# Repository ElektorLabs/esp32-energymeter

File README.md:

# ESP32 Energy Meter

Welcome to the official repository for the ESP32 Energy Meter, an energy monitoring project developed by Elektor Labs. This repository hosts all the necessary design files, code, and documentation to build and deploy a safe energy meter using the ESP32-S3 microcontroller.

## Project Overview

The ESP32 Energy Meter utilizes the Espressif ESP32-S3 microcontroller and the ATM90E32AS IC from Microchip for precise energy measurement across single and three-phase systems. This version includes significant safety and functionality enhancements, including a transformer-based power supply and modularity for diverse applications.

## Features

- **High Precision:** Uses ATM90E32AS IC for accurate energy data.
- **Enhanced Safety:** Transformer-based power reduces direct exposure to high voltages.
- **Flexible Configuration:** Supports both single-phase and three-phase installations.
- **Smart Home Integration:** Easily integrates with Home Assistant for advanced energy management.
- **Customizable Firmware:** Includes ESPHome YAML configurations for easy adaptation and updates.

## Repository Contents

- `/hardware` - Electronic schematic files.
- `/hardware` - PCB design files suitable for manufacturing.
- `/src/ESPHome` - ESPHome YAML configuration files.

## Getting Started

### Prerequisites

Components used in this project are mention in the BOM list `/hardware/production/BOM-esp32-energymeter-V2.xlsx`, overview of the components and required tools are as follows:
- ESP32-S3 module
- ATM90E32AS IC
- Step-down transformer (220V AC to 12V AC) - Preferably a bell transformer
- Current Transfomers - YDHC SCT 013 100A 50mA
- Passive components (resistors, capacitors)
- Tools for PCB assembly and soldering

### Setup Instructions

1. **Clone the repository:**
   ```bash
   git clone https://github.com/ElektorLabs/esp32-energymeter.git
   ```
2. **PCB Assembly:**
   - Refer to the `/hardware` directory and manufacture the PCB using the provided design files.
   - Solder the components onto the PCB as per the layout and schematic details in the `/Schematics` folder.

3. **Firmware Installation:**
   - Navigate to the `/src/ESPHome` directory.
   - Update the YAML file with your specific network details and preferences.
   - Flash the firmware to the ESP32-S3 using ESPHome through the command line or ESPHome Dashboard.

4. **Integrate with Home Assistant:**
   - Follow the integration guide in the article to connect the energy meter to Home Assistant.
   - Monitor and manage your energy consumption directly through the Home Assistant interface.

## Calibration and Testing

- After assembly, perform a calibration check as described in the article to ensure accuracy.
- Test the device under different load conditions to verify the setup and adjust the calibration if necessary.

## Contributing

Your contributions are welcome! If you have enhancements, fixes, or improvements, please fork this repository and submit a pull request with your changes. For substantial modifications or new features, please open an issue to discuss them first.

## License

This project is distributed under the MIT License - see the LICENSE file for details.

## Acknowledgments

- Thanks to Espressif Systems for the ESP32 technology.
- Thanks to Microchip for the energy measurement IC.
- Gratitude to all community members who have contributed to refining this project.

## Contact

For further inquiries or support, feel free to reach out through GitHub issues or the project discussion board.

---

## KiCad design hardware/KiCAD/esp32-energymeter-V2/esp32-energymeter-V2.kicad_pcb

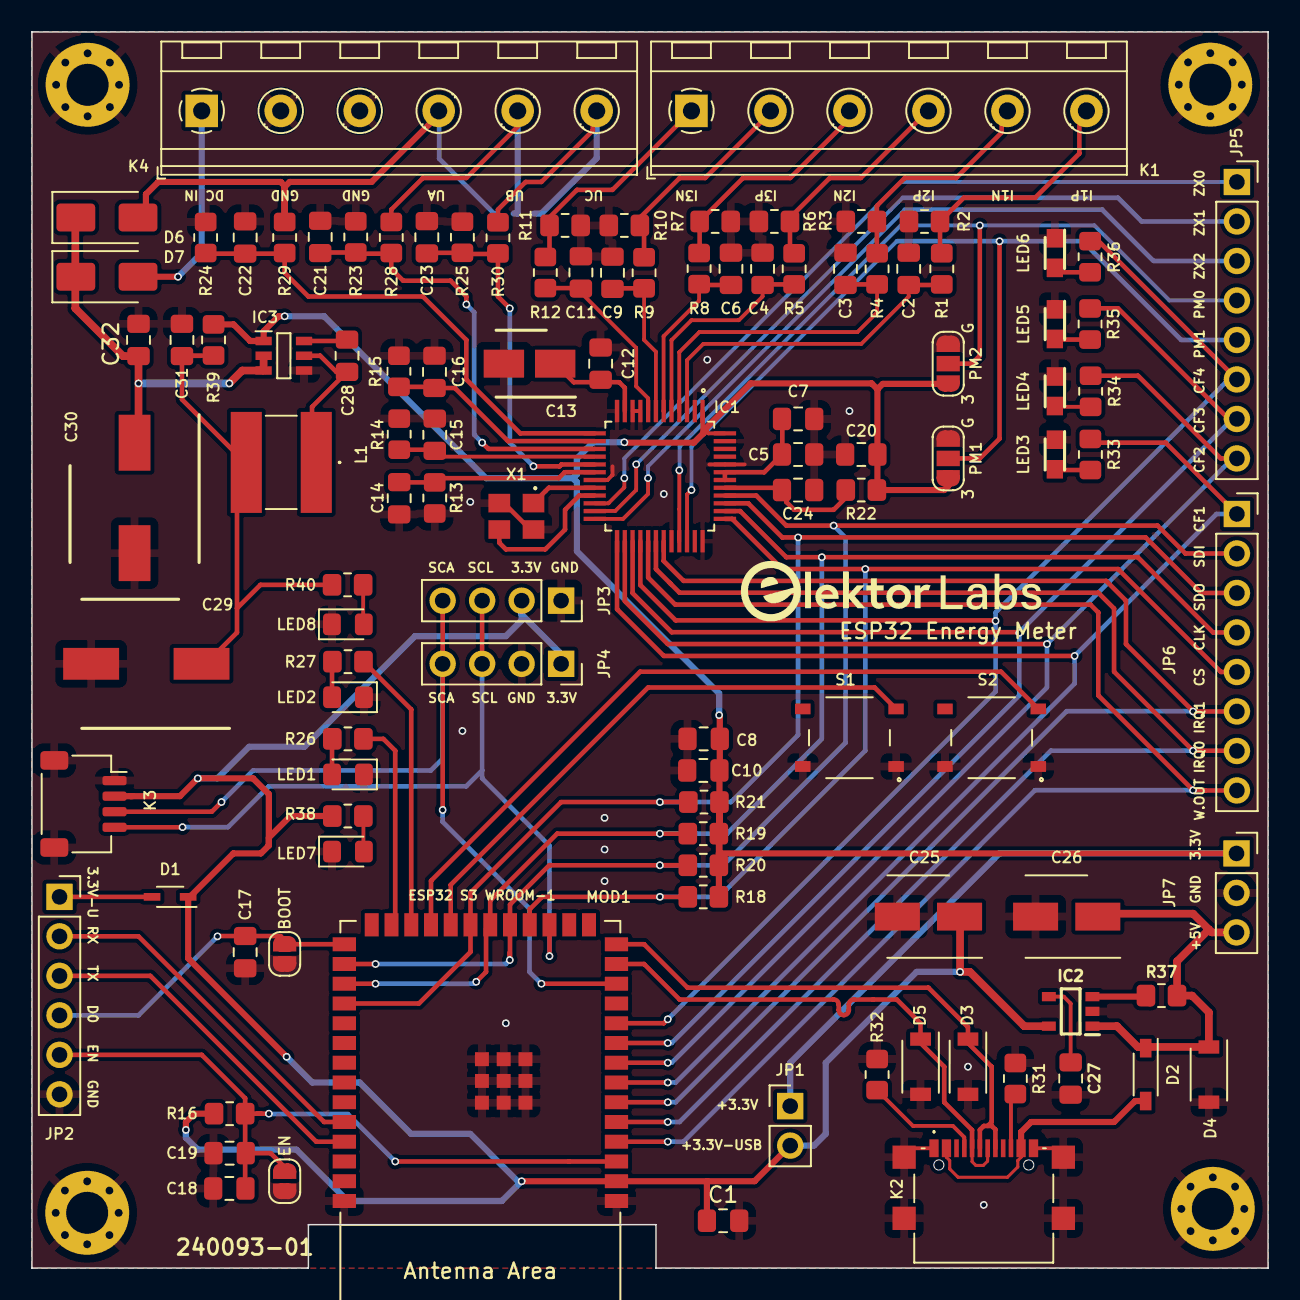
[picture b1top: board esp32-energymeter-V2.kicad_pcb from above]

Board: 2 copper layers, 79.5 x 79.5 mm, 114 parts (1 on the bottom side), 77 nets.

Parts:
BOOT1: BOOT; SolderJumper-2_P1.3mm_Open_RoundedPad1.0x1.5mm
C1, C8, C10, C28, C32: 100nF 50V; C_0805_2012Metric_Pad1.18x1.45mm_HandSolder
C2, C3, C4, C6, C9, C11, C14, C15, C16: 18nF; C_0805_2012Metric_Pad1.18x1.45mm_HandSolder
C5, C12, C17, C18, C19: 0.1uF; C_0805_2012Metric_Pad1.18x1.45mm_HandSolder
C7: 10uF 10V; C_0805_2012Metric_Pad1.18x1.45mm_HandSolder
C13: 10 uF; CAPAE430X550N
C20, C24, C31: 100nF; C_0805_2012Metric_Pad1.18x1.45mm_HandSolder
C21, C22, C23: 18nF 50V; C_0805_2012Metric_Pad1.18x1.45mm_HandSolder
C25, C26: 22uF; CAPAE530X550N
C27: 0.01uF; C_0805_2012Metric_Pad1.18x1.45mm_HandSolder
C29, C30: 220uF; CAPAE830X1050N
D1: BAT760-7; SOD2513X120N
D2: 1N5819HW-7-F; SOD3716X145N
D3, D4, D5: SZSMF4L5.0AT3G; SODFL3824X140N
D6, D7: B140HW-7; D_SMA
EN1: EN; SolderJumper-2_P1.3mm_Open_RoundedPad1.0x1.5mm
H1, H2, H3, H4: MountingHole_Pad; MountingHole_2.7mm_Pad_Via
IC1: ATM90E32AS-AU-R; QFP50P900X900X120-48N
IC2: NJM2882F33-TE1; SOT95P280X130-5N
IC3: AP63203WU-7; SOT95P280X100-6N
JP1: JUMPER; PinHeader_1x02_P2.54mm_Vertical
JP2: Conn_01x06; PinSocket_1x06_P2.54mm_Vertical
JP3: OLED-A; PinSocket_1x04_P2.54mm_Vertical
JP4: OLED-B; PinSocket_1x04_P2.54mm_Vertical
JP5, JP6: Conn_01x08; PinSocket_1x08_P2.54mm_Vertical
JP7: Conn_01x03; PinSocket_1x03_P2.54mm_Vertical
JP8: SolderJumper_3_Open; SolderJumper-3_P1.3mm_Open_RoundedPad1.0x1.5mm_NumberLabels
K1, K4: Screw_Terminal_01x06; TerminalBlock_RND_205-00236_1x06_P5.08mm_Horizontal
K2: GSB1C41110SSHR
K3: Qwiic; JST_SH_SM04B-SRSS-TB_1x04-1MP_P1.00mm_Horizontal
L1: SRN6028C-3R9M; SRN6028C3R9M
LED1, LED7, LED8: NCD0805R1; LED_0805_2012Metric_Pad1.15x1.40mm_HandSolder
LED2: NCD0805G1; LED_0805_2012Metric_Pad1.15x1.40mm_HandSolder
LED3: 150080RS75000; LEDM2012X80N
LED4: 150080GS75000; LEDM2012X80N
LED5: 150080BS75000; LEDM2012X80N
LED6: 150080AS75000; LEDM2012X80N
MOD1: ESP32-S3-WROOM-1
PM1, PM2: SolderJumper_3_Open; SolderJumper-3_P1.3mm_Open_RoundedPad1.0x1.5mm_NumberLabels
R1, R4, R5, R8, R9, R12, R23, R24, R25: 1k; R_0805_2012Metric_Pad1.20x1.40mm_HandSolder
R2, R3, R6, R7, R10, R11: 2R4; R_0805_2012Metric_Pad1.20x1.40mm_HandSolder
R13, R14, R15: 1K; R_0805_2012Metric_Pad1.20x1.40mm_HandSolder
R16: 10K; R_0805_2012Metric_Pad1.20x1.40mm_HandSolder
R18, R19, R20, R21, R22: 10k; R_0805_2012Metric_Pad1.20x1.40mm_HandSolder
R26, R27, R33, R34, R35, R36, R38, R40: 80R; R_0805_2012Metric_Pad1.20x1.40mm_HandSolder
R28, R29, R30, R37: 100k; R_0805_2012Metric_Pad1.20x1.40mm_HandSolder
R31, R32: 4.7k; R_0805_2012Metric_Pad1.20x1.40mm_HandSolder
R39: 0R; R_0805_2012Metric_Pad1.20x1.40mm_HandSolder
S1, S2: PTS526_SM15_SMTR2_LFS; PTS526SM15SMTR2LFS
X1: ABM8G-16.384MHZ-B4Y-T; ABM8G

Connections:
+3.3V: C8.1, C10.1, C20.1, IC1.1 (AVDD), IC1.48 (DVDD), IC3.1 (FB), JP1.1, JP7.1, PM1.1 (A), PM2.1 (A), R18.2, R19.2, R20.2, R21.2, R22.1, R39.1
+5VA: C26.1 (+), D2.1 (K), D4.1 (K), IC2.1 (VIN), JP7.3, R37.2
+12V: C30.1 (+), C32.2, D6.1 (K), D7.1 (K), IC3.2 (EN), IC3.3 (VIN)
/DC IN: D7.2 (A), K4.1
/UA: D6.2 (A), JP8.3 (B), K4.4, R29.2
/UB: JP8.2 (C), K4.5, R28.2
/UC: JP8.1 (A), K4.6, R30.2
/VBUS: D2.2 (A), K2.A4 (VBUS_1), K2.A9 (VBUS_2)
CF1: IC1.25 (CF1), JP6.1, MOD1.7 (GPIO7/TOUCH7/ADC1_CH6), R33.2
CF2: IC1.26 (CF2), JP5.8, MOD1.8 (GPIO15/U0RTS/ADC2_CH4/XTAL_32K_P), R34.2
CF3: IC1.27 (CF3), JP5.7, MOD1.9 (GPIO16/U0CTS/ADC2_CH5/XTAL_32K_N), R35.2
CF4: IC1.28 (CF4), JP5.6, MOD1.10 (GPIO17/U1TXD/ADC2_CH6), R36.2
CLK: IC1.38 (SCLK), JP6.4, MOD1.20 (GPIO12/TOUCH12/ADC2_CH1/FSPICLK/FSPIIO6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), MOD1.29 (SPIIO7/GPIO36/FSPICLK/SUBSPICLK), R19.1
CS: IC1.37 (~CS), JP6.5, MOD1.18 (GPIO10/TOUCH10/ADC1_CH9/FSPICS0/FSPIIO4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), R18.1
D0: BOOT1.1 (A), C17.1, JP2.4, MOD1.27 (GPIO0/BOOT)
EN: C18.1, C19.1, EN1.1 (A), JP2.5, MOD1.3 (EN), R16.1
GND: BOOT1.2 (B), C1.2, C2.2, C3.1, C4.2, C5.2, C6.1, C7.2, C8.2, C9.2, C10.2, C11.1, C12.2, C13.2 (-), C14.2, C15.2, C16.2, C17.2, C18.2, C19.2, C20.2, C21.2, C22.2, C23.2, C24.2, C25.2 (-), C26.2 (-), C27.1, C29.2 (-), C30.2 (-), C31.2, C32.1, D3.2 (A), D4.2 (A), D5.2 (A), EN1.2 (B), H1.1, H2.1, H3.1, H4.1, IC1.2 (AGND), IC1.9 (IC), IC1.10 (IC), IC1.12 (AGND), IC1.19 (DGND), IC1.32 (TEST), IC1.36 (IC), IC1.44 (DGND), IC1.47 (DGND), IC2.2 (GND), IC3.4 (GND), JP2.6, JP3.1, JP4.2, JP7.2, K2.A1 (GND_1), K2.A12 (GND_2), K2.MP1, K2.MP2, K2.MP3, K2.MP4, K3.1, K3.MP (MountPin), K4.2, K4.3, LED1.1 (K), LED2.1 (K), LED3.1 (K), LED4.1 (K), LED5.1 (K), LED6.1 (K), LED7.1 (K), LED8.1 (K), MOD1.1 (GND), MOD1.40 (GND), MOD1.41 (GND), PM1.3 (B), PM2.3 (B), R2.1, R3.2, R6.1, R7.2, R10.1, R11.2, R13.1, R14.2, R15.2, R23.1, R24.1, R25.1, R31.1, R32.2, S1.1 (COM_1), S1.2 (COM_2), S2.1 (COM_1), S2.2 (COM_2), X1.2 (GND_1), X1.4 (GND_2)
GPIO14: MOD1.22 (GPIO14/TOUCH14/ADC2_CH3/FSPIWP/FSPIDQS/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), S1.3 (NO_1)
GPIO21: MOD1.23 (GPIO21), S2.3 (NO_1)
IRQ0: IC1.30 (IRQ0), JP6.7, MOD1.5 (GPIO5/TOUCH5/ADC1_CH4)
IRQ1: IC1.31 (IRQ1), JP6.6, MOD1.6 (GPIO6/TOUCH6/ADC1_CH5)
LED_GREEN: MOD1.24 (GPIO47/SPICLK_P/SUBSPICLK_P_DIFF), R27.2
LED_RED: MOD1.25 (GPIO48/SPICLK_N/SUBSPICLK_N_DIFF), R26.2
unnamed: C5.1, C7.1, IC1.42 (VDD18), IC1.43 (VDD18)
unnamed: C12.1, C13.1 (+), IC1.11 (VREF)
unnamed: C29.1 (+), C31.1, L1.2, R39.2, R40.2
unnamed: D1.2 (A), JP2.1
unnamed: C3.2, IC1.4 (I1N), R4.1
unnamed: C2.1, IC1.3 (I1P), R1.1
unnamed: C6.2, IC1.6 (I2N), R8.1
unnamed: C4.1, IC1.5 (I2P), R5.1
unnamed: C11.2, IC1.8 (I3N), R12.1
unnamed: C9.1, IC1.7 (I3P), R9.1
unnamed: IC1.20 (OSCI), X1.1 (XTAL_1)
unnamed: IC1.21 (OSCO), X1.3 (XTAL_2)
unnamed: C16.1, IC1.14 (V1N), R15.1
unnamed: C22.1, IC1.13 (V1P), R24.2, R29.1
unnamed: C15.1, IC1.16 (V2N), R14.1
unnamed: C21.1, IC1.15 (V2P), R23.2, R28.1
unnamed: C14.1, IC1.18 (V3N), R13.2
unnamed: C23.1, IC1.17 (V3P), R25.2, R30.1
unnamed: IC2.3 (CONTROL_(ACTIVE_HIGH)), R37.1
unnamed: C27.2, IC2.4 (NOISE_BYPASS)
unnamed: C28.1, IC3.6 (BST)
unnamed: C28.2, IC3.5 (SW), L1.1
unnamed: K1.1, R11.1, R12.2
unnamed: K1.2, R9.2, R10.2
unnamed: K1.3, R7.1, R8.2
unnamed: K1.4, R5.2, R6.2
unnamed: K1.5, R3.1, R4.2
unnamed: K1.6, R1.2, R2.2
unnamed: K2.A5 (CC1), R32.1
unnamed: K2.B5 (CC2), R31.2
unnamed: LED1.2 (A), R26.1
unnamed: LED2.2 (A), R27.1
unnamed: LED3.2 (A), R33.1
unnamed: LED4.2 (A), R34.1
unnamed: LED5.2 (A), R35.1
unnamed: LED6.2 (A), R36.1
unnamed: LED7.2 (A), R38.1
unnamed: LED8.2 (A), R40.1
PM0: IC1.33 (PM0), JP5.4, PM2.2 (C)
PM1: IC1.34 (PM1), JP5.5, PM1.2 (C)
RESET: C24.1, IC1.41 (~RESET), R22.2
RX0: JP2.2, MOD1.36 (U0RXD/GPIO44/CLK_OUT2)
SCL: JP3.3, JP4.3, K3.4, MOD1.17 (GPIO9/TOUCH9/ADC1_CH8/FSPIHD/SUBSPIHD)
SDA: JP3.4, JP4.4, K3.3, MOD1.12 (GPIO8/TOUCH8/ADC1_CH7/SUBSPICS1)
SDI: IC1.40 (SDI), JP6.2, MOD1.19 (GPIO11/TOUCH11/ADC2_CH0/FSPID/FSPIIO5/S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), MOD1.28 (SPIIO6/GPIO35/FSPID/SUBSPID), R20.1
SDO: IC1.39 (SDO), JP6.3, MOD1.21 (GPIO13/TOUCH13/ADC2_CH2/FSPIQ/FSPIIO7/S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), MOD1.30 (SPIDQS/GPIO37/FSPIQ/SUBSPIQ), R21.1
TX0: JP2.3, MOD1.37 (U0TXD/GPIO43/CLK_OUT1)
USB_+3.3V: C1.1, C25.1 (+), D1.1 (K), IC2.5 (VOUT), JP1.2, JP3.2, JP4.1, K3.2, MOD1.2 (3V3), R16.2, R38.2
USB_DN: D5.1 (K), K2.A7 (DN1), K2.B7 (DN2), MOD1.13 (GPIO19/U1RTS/ADC2_CH8/CLK_OUT2/USB_D-)
USB_DP: D3.1 (K), K2.A6 (DP1), K2.B6 (DP2), MOD1.14 (GPIO20/U1CTS/ADC2_CH9/CLK_OUT1/USB_D+)
WARNOUT: IC1.29 (WARNOUT), JP6.8, MOD1.4 (GPIO4/TOUCH4/ADC1_CH3)
ZX0: IC1.22 (ZX0), JP5.1
ZX1: IC1.23 (ZX1), JP5.2
ZX2: IC1.24 (ZX2), JP5.3

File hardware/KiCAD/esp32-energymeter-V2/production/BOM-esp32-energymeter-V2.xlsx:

|  | Date: |  | 45352.696527777778
 |  | Ref | Non Replaceable | Mouser Number | 5 Qty | Qty | Value | Cmp name | Footprint | Description
 |  | C1, C5, C7, C8, C10, C12, C17, C18, C19, C20, C24, C27, C28, C31, C32 |  | 80-C0805C104M5RAC | 75 | 15 | 100nF | C0805C104M5RAC | Capacitor_SMD:C_0805_2012Metric_Pad1.18x1.45mm_HandSolder | Unpolarized capacitor
 |  | C2, C3, C4, C6, C9, C11, C14, C15, C16, C21, C22, C23 |  | 80-C0805C183K2RACTU | 60 | 12 | 18nF | C0805C183K2RACTU | Capacitor_SMD:C_0805_2012Metric_Pad1.18x1.45mm_HandSolder | Unpolarized capacitor
 |  | C13 |  | 710-865090340001 | 5 | 1 | 4.7uF | 8.6509E+11 | SamacSys_Parts:CAPAE430X550N | Wurth Elektronik 4.7uF 16 V dc Aluminium Electrolytic Capacitor, WCAP-ASLU Seri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
 |  | C25, C26 |  | 710-865080442004 | 10 | 2 | 22uF | 8.6508E+11 | CAPAE530X550N | Wurth Elektronik 22uF Electrolytic Capacitor 25V 20% Surface Mount - 8650804420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
 |  | C29, C30 |  | 710-865080553014 | 10 | 2 | 220uF | 8.65081E+11 | CAPAE830X1050N | Wurth Elektronik 220uF 35 V dc Aluminium Electrolytic Capacitor, WCAP-ASLI Seri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
 |  | D1 | x | 621-BAT760-7 | 5 | 1 | BAT760-7 | BAT760-7 | SOD2513X120N | Diode Schottky 30V 1A 2Pin SOD323 Diodes Inc BAT760-7, SMT Schottky Diode, 30V 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
 |  | D2 | x | 621-1N5819HW-F | 5 | 1 | 1N5819HW-7-F | 1N5819HW-7-F | SOD3716X145N | Diode Schottky 1A 40V SOD123 Diodes Inc 1N5819HW-7-F, SMT Schottky Diode, 40V 1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
 |  | D3, D4, D5 | x | 576-SZSMF4L5.0AT3G | 15 | 3 | SZSMF4L5.0AT3G | SZSMF4L5.0AT3G | SODFL3824X140N | Automotive Surface Mount 400 W TVS Diode in SOD-123FL
 |  | D6,D7 | x | 621-B140HW-7 | 5 | 1 | B140HW-7 | B140HW-7 | SOD3716X145N | Diodes Inc B140HW-7, SMT Schottky Diode, 40V 1A, 2-Pin SOD-123
 |  | IC1 | x | 556-ATM90E32AS-AU-R | 5 | 1 | ATM90E32AS-AU-R | ATM90E32AS-AU-R | ATM90E32AS-AU-R:QFP50P900X900X120-48N
 |  | IC2 | x | 513-NJM2882F33-TE1 | 5 | 1 | NJM2882F33-TE1 | NJM2882F33-TE1 | Package_TO_SOT_SMD:SOT-23-5 | LDO Voltage Regulators 75dB 30uVrms 300mA 1.0uF 3.3V 350mW
 |  | IC3 | x | 621-AP63203WU-7 | 5 | 1 | AP63203WU-7 | AP63203WU-7 | SOT95P280X100-6N | Switching Voltage Regulators DCDC Conv HV Buck TSOT26 T&R 3K
 |  | K1, K4 |  | 490-TB004-508-06BE | 10 | 2 |  | Screw_Terminal_01x06 | TerminalBlock_RND:TerminalBlock_RND_205-00236_1x06_P5.08mm_Horizontal | Terminal block, screw type, 5.08 , horizontal, 6 poles, CUI Blue
 |  | K2 |  | 523-GSB1C41110SSHR | 5 | 1 | GSB1C41110SSHR | GSB1C41110SSHR | GSB1C41110SSHR | USB2.0, Type C, Top mount, Center Height 1.63mm, Single Row Surface Mount
 |  | L1 |  | 652-SRN6028C-3R9M | 5 | 1 | 3.9uH | SRN6028C-3R9M | SRN6028C3R9M | Ind,6.0x6.0x2.6mm,3.9uH+/-20%,3.3A,shd
 |  | LED3, LED4, LED5, LED6 |  | 710-150080YS75000 | 20 | 4 | Yellow Led | 150080YS75000 | LED_SMD:LED_0805_2012Metric_Pad1.15x1.40mm_HandSolder | Light emitting diode
 |  | MOD1 | x | 356-ESP32-S3WRM1N8R2 | 5 | 1 | ESP32-S3-WROOM-1 | ESP32-S3-WROOM-1-N8R2 | PCM_Espressif:ESP32-S3-WROOM-1 | 2.4 GHz WiFi (802.11 b/g/n) and Bluetooth Â® 5 (LE) module Built around ESP32S3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
 |  | R1, R4, R5, R8, R9, R12, R13, R14, R15, R23, R24, R25 |  | 652-CHP0805FX1001ELF | 60 | 12 | 1k | R_US | Resistor_SMD:R_0805_2012Metric_Pad1.20x1.40mm_HandSolder | Resistor
 |  | R2, R3, R6, R7, R10, R11 |  | 755-SDR10EZPJ2R4 | 30 | 6 | 2R4 | R_US | Resistor_SMD:R_0805_2012Metric_Pad1.20x1.40mm_HandSolder | Resistor
 |  | R16, R18, R19, R20, R21, R22 |  | 652-CMP0805-FX-1002L | 30 | 6 | 10k | R_US | Resistor_SMD:R_0805_2012Metric_Pad1.20x1.40mm_HandSolder | Resistor
 |  | R28, R29, R30, R37 |  | 652-CMP0805-FX-1003L | 20 | 4 | 100k | R_US | Resistor_SMD:R_0805_2012Metric_Pad1.20x1.40mm_HandSolder | Resistor
 |  | R31, R32 |  | 755-SDR10EZPJ472 | 10 | 2 | 4.7k | R_US | Resistor_SMD:R_0805_2012Metric_Pad1.20x1.40mm_HandSolder | Resistor
 |  | R26, R27, R33, R34, R35, R36, R38, R40 |  | 660-RK73H2ATTD80R6F | 40 | 8 | 80R | R_US | Resistor_SMD:R_0805_2012Metric_Pad1.20x1.40mm_HandSolder | Resistor
 |  | R39 |  | 71-RCS08050000Z0EA | 5 | 1 | 0R | R_US | Resistor_SMD:R_0805_2012Metric_Pad1.20x1.40mm_HandSolder | Resistor
 |  | S1, S2 |  | 611-PTS526SM15SMTR2L | 10 | 2 |  | PTS526_SM15_SMTR2_LFS | PTS526SM15SMTR2LFS | Tactile Switches 50mA 12VDC, 5.2x5.2mm, 1.5mm H, 160gf, G leads, No ground pin,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
 |  | X1 | x | 815-ABM8G-16.3-B4Y-T | 5 | 1 |  | ABM8G-16.384MHZ-B4Y-T | ABM8G | 16.384 MHz +/-30ppm Crystal 10pF 80 Ohms 4-SMD, No Lead
 |  | LED1, LED 7, LED 8 |  | 710-150080RS75000 | 15 | 3 | Red | 150080RS75000 | LED_SMD:LED_0805_2012Metric_Pad1.15x1.40mm_HandSolder | Light emitting diode
 |  | LED2 |  | 710-150080GS75000 | 5 | 1 | Green Led | 150080GS75000
 |  | Step Down Voltage Transformer
 |  | Navaris deurbeltransformator - 8V, 12V, 24V |  |  | 16 EUR | https://amzn.eu/d/h4jTlUE
 |  | Honeywell E3539N beltransformator VDE 2 - 12V |  |  | 22 EUR | https://amzn.eu/d/geya4uD
 |  | Honeywell E3554N Klingeltransormator VDE 3 - 8V |  |  | 14 EUR | https://amzn.eu/d/geya4uD
 |  | Current Transformer
 |  | YHDC SCT 013 100A-50mA |  |  | 4 EUR | https://www.poweruc.pl/products/split-core-current-transform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

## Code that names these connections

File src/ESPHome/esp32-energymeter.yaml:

esphome:
  name: esp32-energymeter
  friendly_name: esp32_energymeter

esp32:
  board: esp32-s3-devkitc-1
  framework:
    type: arduino


# Enable logging
logger:

# Enable Home Assistant API
api:
  encryption:
    key: "xxxx"

ota:
  password: "xxxx"

wifi:
  ssid: !secret wifi_ssid
  password: !secret wifi_password

  # Enable fallback hotspot (captive portal) in case wifi connection fails
  ap:
    ssid: "xxx"
    password: "xxx"

captive_portal:

i2c:
  sda: GPIO8 
  scl: GPIO9 
  scan: True


spi:
  clk_pin: GPIO12
  miso_pin: GPIO13
  mosi_pin: GPIO11

sensor:
  - platform: atm90e32
    cs_pin: GPIO10
    phase_a:
      voltage:
        name: "Line Voltage A"
        id: VAC
      current:
        name: "CT1 Current"
        id: ct1Amps
      power:
        name: "Active Power CT1"
      reactive_power:
        name: "Reactive Power CT1"
      power_factor:
        name: "Power Factor CT1"
      gain_voltage: 59598
      gain_ct: 64596
    phase_b:
      voltage: 
        name: "Line Voltage B"
        id: VBC
      current:
        name: "CT2 Current"
        id: ct2Amps
      power:
        name: "Active Power CT2"
      reactive_power:
        name: "Reactive Power CT2"
      power_factor:
        name: "Power Factor CT2"
      gain_voltage: 59417 
      gain_ct: 60366
    phase_c:
      voltage: 
        name: "Line Voltage C"
        id: VCC
      current:
        name: " CT3 Current"
        id: ct3Amps
      power:
        name: "Active Power CT3"
      reactive_power:
        name: "Reactive Power CT3"
      power_factor:
        name: "Power Factor CT3"
      gain_voltage: 59365
      gain_ct: 61366
    frequency:
      name: "Line Frequency"
    chip_temperature:
      name: "Chip Temperature"
    line_frequency: 50Hz
    current_phases: 2
    gain_pga: 2X
    update_interval: 5s

#Watts per channel
  - platform: template
    name: CT1 Watts
    id: ct1Watts
    lambda: return id(ct1Amps).state * id(VAC).state;
    accuracy_decimals: 0
    unit_of_measurement: W
    icon: "mdi:flash-circle"
    update_interval: 5s
  - platform: template
    name: CT2 Watts
    id: ct2Watts
    lambda: return id(ct2Amps).state * id(VCC).state;
    accuracy_decimals: 0
    unit_of_measurement: W
    icon: "mdi:flash-circle"
    update_interval: 5s
  - platform: template
    name: CT3 Watts
    id: ct3Watts
    lambda: return id(ct3Amps).state * id(VCC).state;
    accuracy_decimals: 0
    unit_of_measurement: W
    icon: "mdi:flash-circle"
    update_interval: 5s
#Total Amps
  - platform: template
    name: Total Amps
    id: totalAmps
    lambda: return id(ct1Amps).state + id(ct2Amps).state + id(ct3Amps).state;
    accuracy_decimals: 2
    unit_of_measurement: A
    icon: "mdi:flash"
    update_interval: 5s
#Total Watts
  - platform: template
    name: Total Watts
    id: totalWatts
    lambda: return id(totalAmps).state * id(VAC).state;
    accuracy_decimals: 1
    unit_of_measurement: W
    icon: "mdi:flash-circle"
    update_interval: 5s
#kWh
  - platform: total_daily_energy
    name: Total kWh
    power_id: totalWatts
    filters:
      - multiply: 0.001
    unit_of_measurement: kWh

time:
  - platform: sntp
    id: sntp_time
  

display:
  - platform: ssd1306_i2c
    model: "SSD1306 128x64"
    reset_pin: 16  # Change to your OLED's reset pin if needed
    address: 0x3C  # Typically 0x3C or 0x3D, check your device specifications
    rotation: 180

    lambda: |-
      it.strftime(0, 0, id(roboto_medium), TextAlign::TOP_LEFT, "%H:%M:%S", id(sntp_time).now());
      it.printf(0, 10, id(roboto_medium), TextAlign::TOP_LEFT, "Total kW: %.3f", id(totalWatts).state * 0.001);
      it.printf(0, 25, id(roboto_medium), TextAlign::TOP_LEFT, "CA: %.1f A", id(ct1Amps).state);
      it.printf(45, 25, id(roboto_medium), TextAlign::TOP_LEFT, "CB: %.1f A", id(ct2Amps).state);
      it.printf(90, 25, id(roboto_medium), TextAlign::TOP_LEFT, "CC: %.1f A", id(ct3Amps).state);
      it.printf(0, 40, id(roboto_medium), TextAlign::TOP_LEFT, "VA: %.1f V", id(VAC).state);
      it.printf(70, 40, id(roboto_medium), TextAlign::TOP_LEFT, "VB: %.1f V", id(VBC).state);
      it.printf(0, 50, id(roboto_medium), TextAlign::TOP_LEFT, "VC: %.1f V", id(VCC).state);

font:
  - file: "fonts/Roboto-Medium.ttf"
    id: roboto_medium
    size: 8

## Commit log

2024-06-25 updated the BOM
    Mentioned which components should NOT be replaced. The ones with "x" should not be replated with equivalent components.
2024-06-25 added mechanical and drawing files
    Added Mechanical and Drawing files.
    > PDF Drawing file
    > DWG
    > DXF
    > .STEP [file of the entire PCB]
2024-06-26 added images
2024-06-26 minor fix
    there were some resistors in the schematic where there was a typo, it was "10K" it should be "10k".
2024-07-07 Update esp32-energymeter.yaml
    The id CT2 and CT3 were interchanged.
2024-07-31 updated bom
    updated bom lists, mouser and main project bom.
2024-08-05 bom update
2024-11-18 added
    STL files of the enclosure for the energy meter.
2024-12-05 updated
    Added the Arduino IDE based code for the ESP32 Energy Meter that sends data to Home Assistant via MQTT.
